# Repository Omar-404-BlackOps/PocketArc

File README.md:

# PocketArc
A simple programmable pocket-sized 3-buttons game console based on Raspberry Pi Pico for simple games such as "Guess the number" and so on.

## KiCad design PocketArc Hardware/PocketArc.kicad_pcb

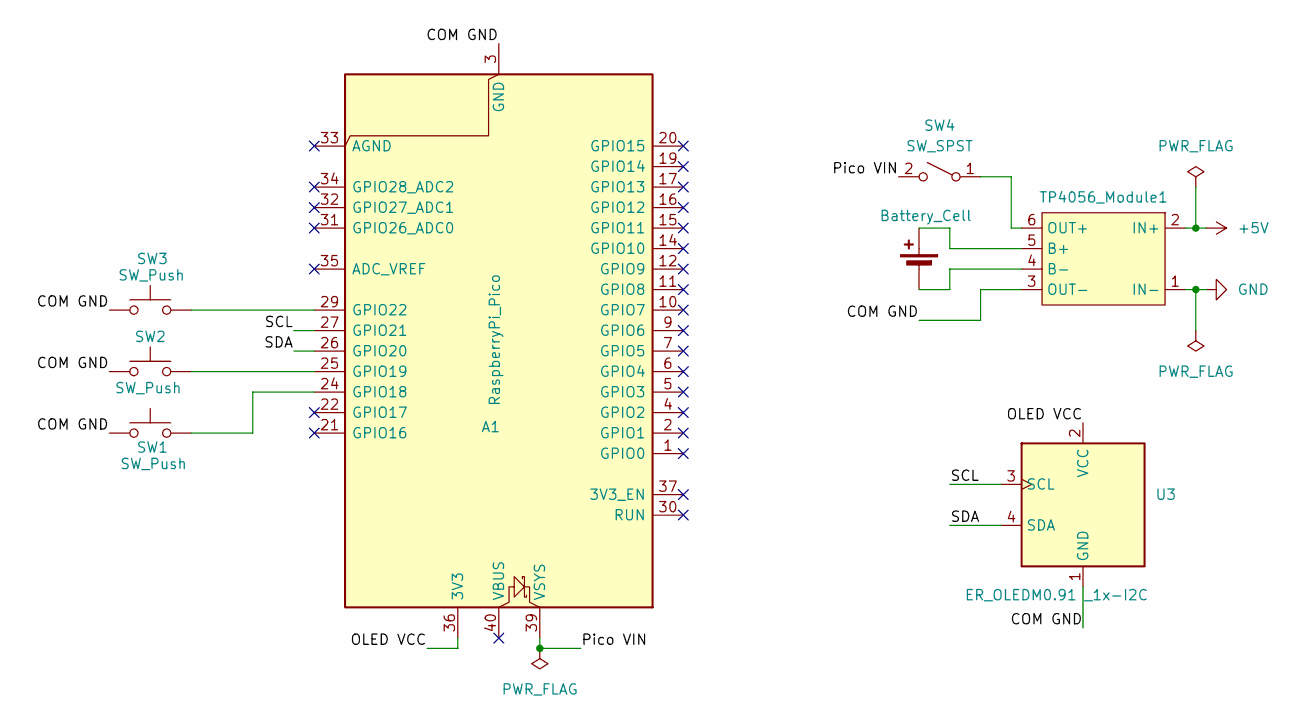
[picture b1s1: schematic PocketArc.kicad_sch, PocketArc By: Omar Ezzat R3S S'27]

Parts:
A1: RaspberryPi_Pico; RaspberryPi_Pico_Common_Unspecified
BT1: Battery_Cell; BatteryHolder_Keystone_1042_1x18650_Back Version
SW1, SW2, SW3: SW_Push; Push Button 12mm
SW4: SW_SPST; KCD11-101 Rocker Switch BV
TP4056_Module1: TP4056_Module; TP4056 Li-Ion Battery Charger Module_Back Version
U3: ER_OLEDM0.91 _1x-I2C; OLED I2C 1.3 Module

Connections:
+5V: TP4056_Module1.2 (IN+)
/COM GND: A1.3 (GND), A1.8 (GND), A1.13 (GND), A1.18 (GND), A1.23 (GND), A1.28 (GND), A1.38 (GND), SW1.2, SW2.1, SW3.1, TP4056_Module1.3 (OUT-), U3.1 (GND)
/OLED VCC: A1.36 (3V3), U3.2 (VCC)
/Pico VIN: A1.39 (VSYS), SW4.2 (B)
/SCL: A1.27 (GPIO21), U3.3 (SCL)
/SDA: A1.26 (GPIO20), U3.4 (SDA)
GND: TP4056_Module1.1 (IN-)
unnamed: A1.24 (GPIO18), SW1.1
unnamed: A1.25 (GPIO19), SW2.2
unnamed: A1.29 (GPIO22), SW3.2
unnamed: BT1.1 (+), TP4056_Module1.5 (B+)
unnamed: BT1.2 (-), TP4056_Module1.4 (B-)
unnamed: SW4.1 (A), TP4056_Module1.6 (OUT+)

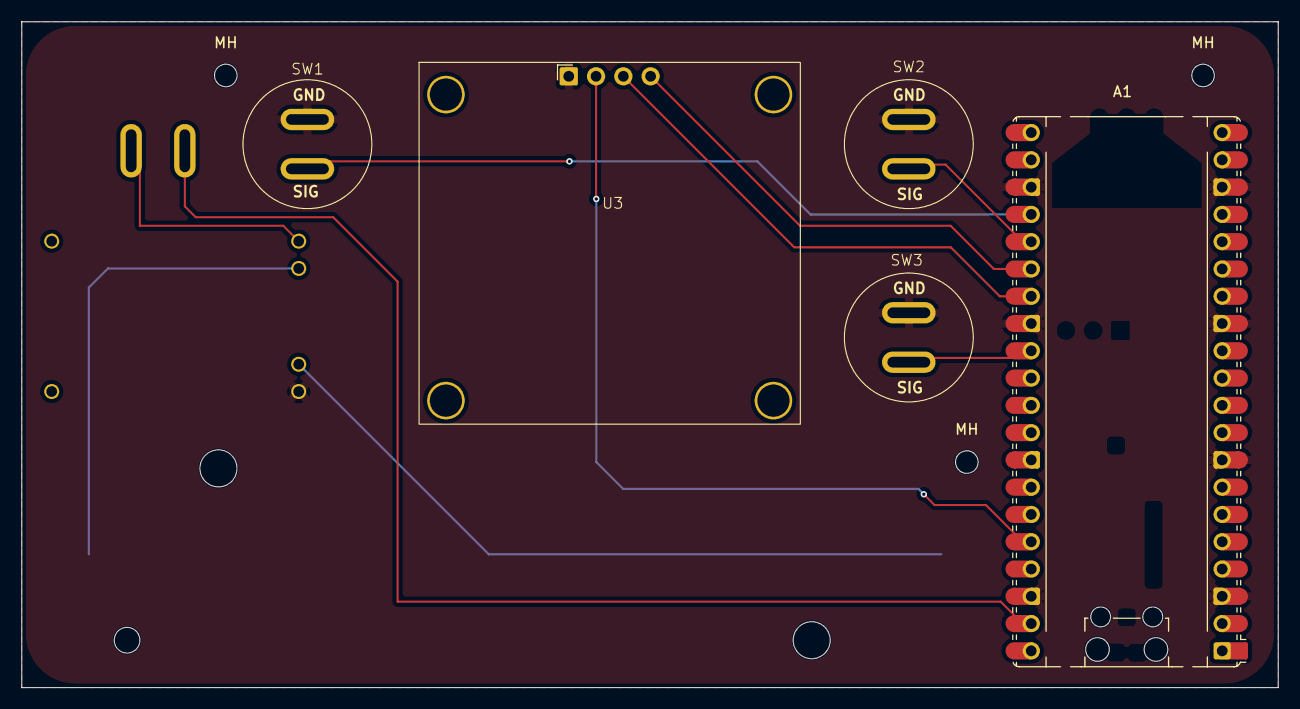
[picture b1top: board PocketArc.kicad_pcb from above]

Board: 2 copper layers, 117.0 x 62.0 mm, 11 parts (0 on the bottom side), 11 nets.

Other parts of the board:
MH: MountingHole_2.1mm
MH#2, MH#3: MountingHole_2.1mm
